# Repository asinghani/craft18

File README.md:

# Craft18

Bring Minecraft Redstone circuits to life using Craft18, our physical re-creation of the game’s “circuit” mechanics using only discrete analog components. Look ma, no microcontrollers! To build even more complex circuits, link the physical world to the virtual world using our custom game plugin and game-to-physical bridge!

Also see our [circuit diagrams PDF](doc/schem.pdf) to see how each circuit is implemented!

## Repo Structure

- [3D printable CAD models for each block](3d_cad/)
- [Texture images for each block](textures/)
- [Raw circuit schematic files](schematics/)
- [Spigot plugin for physical-to-virtual bridge](craft18_plugin/)
- [Software for physical-to-virtual bridge](craft18duino/)
- [Baseplate CAD files](2d_cad/)
- [Connector board layouts](boards/)

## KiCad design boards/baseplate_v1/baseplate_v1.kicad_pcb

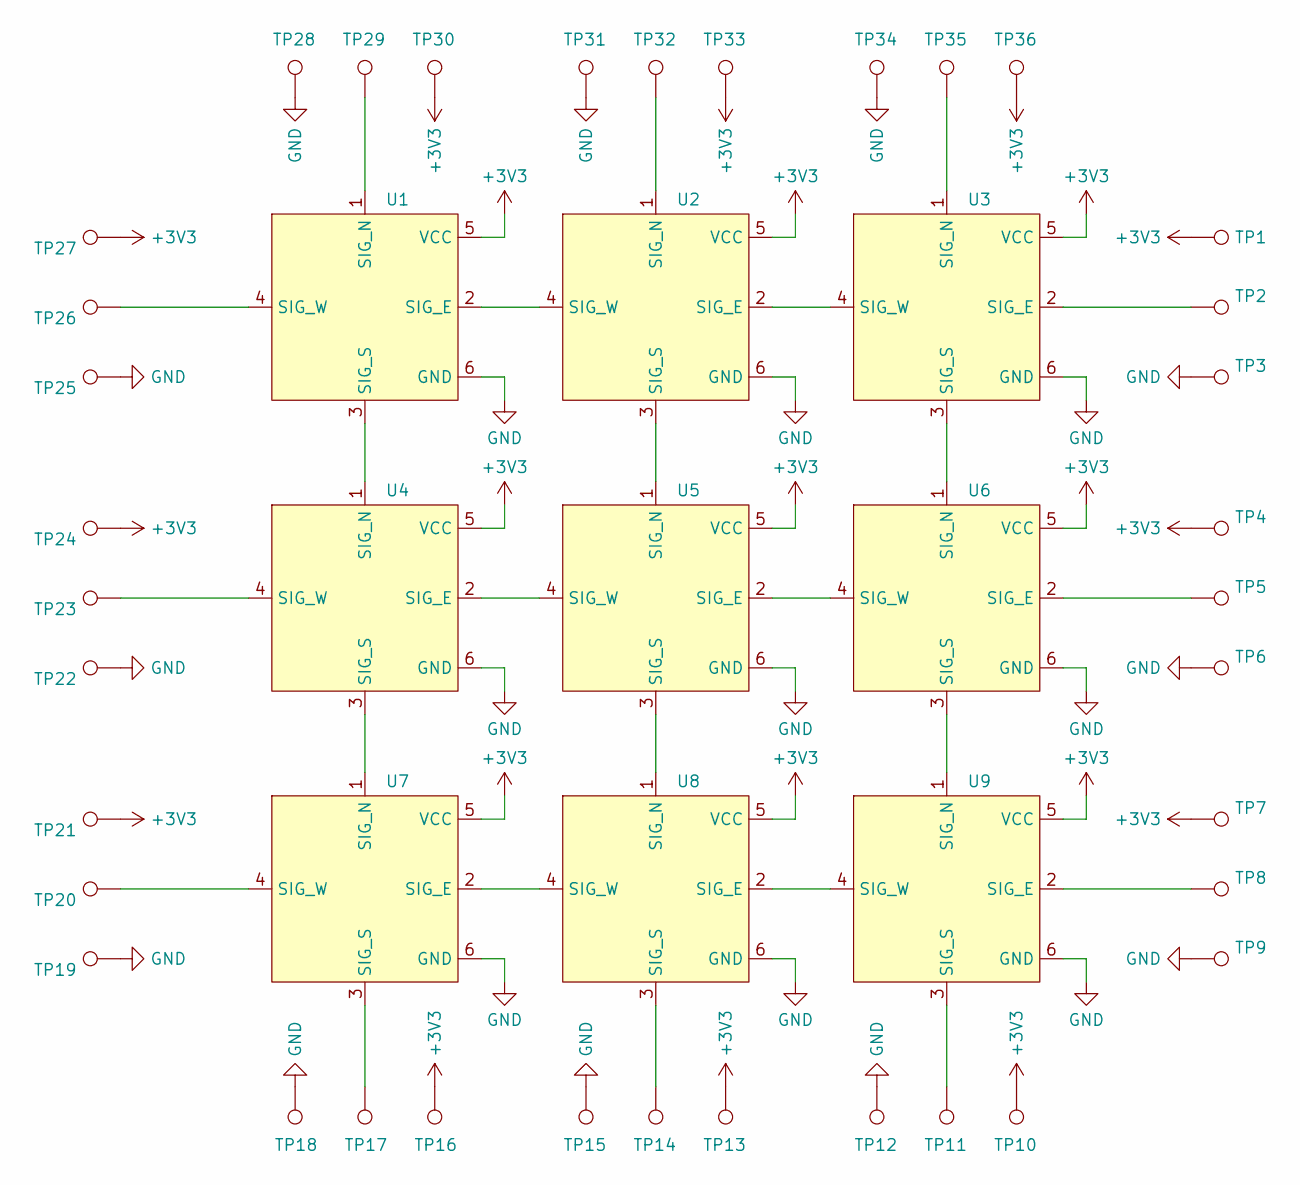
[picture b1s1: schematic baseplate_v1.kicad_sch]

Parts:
TP1, TP2, TP3, TP4, TP5, TP6, TP7, TP8, TP9, TP10, TP11, TP12, TP13, TP14, TP15, TP16, TP17, TP18, TP19, TP20, TP21, TP22, TP23, TP24, TP25, TP26, TP27, TP28, TP29, TP30, TP31, TP32, TP33, TP34, TP35, TP36: TestPoint; edge_pad
U1, U2, U3, U4, U5, U6, U7, U8, U9: 3x3conn

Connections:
+3V3: TP1.1, TP4.1, TP7.1, TP10.1, TP13.1, TP16.1, TP21.1, TP24.1, TP27.1, TP30.1, TP33.1, TP36.1, U1.5 (VCC), U2.5 (VCC), U3.5 (VCC), U4.5 (VCC), U5.5 (VCC), U6.5 (VCC), U7.5 (VCC), U8.5 (VCC), U9.5 (VCC)
GND: TP3.1, TP6.1, TP9.1, TP12.1, TP15.1, TP18.1, TP19.1, TP22.1, TP25.1, TP28.1, TP31.1, TP34.1, U1.6 (GND), U2.6 (GND), U3.6 (GND), U4.6 (GND), U5.6 (GND), U6.6 (GND), U7.6 (GND), U8.6 (GND), U9.6 (GND)
unnamed: U1.2 (SIG_E), U2.4 (SIG_W)
unnamed: TP29.1, U1.1 (SIG_N)
unnamed: U1.3 (SIG_S), U4.1 (SIG_N)
unnamed: TP26.1, U1.4 (SIG_W)
unnamed: U2.2 (SIG_E), U3.4 (SIG_W)
unnamed: TP32.1, U2.1 (SIG_N)
unnamed: U2.3 (SIG_S), U5.1 (SIG_N)
unnamed: TP2.1, U3.2 (SIG_E)
unnamed: TP35.1, U3.1 (SIG_N)
unnamed: U3.3 (SIG_S), U6.1 (SIG_N)
unnamed: U4.2 (SIG_E), U5.4 (SIG_W)
unnamed: U4.3 (SIG_S), U7.1 (SIG_N)
unnamed: TP23.1, U4.4 (SIG_W)
unnamed: U5.2 (SIG_E), U6.4 (SIG_W)
unnamed: U5.3 (SIG_S), U8.1 (SIG_N)
unnamed: TP5.1, U6.2 (SIG_E)
unnamed: U6.3 (SIG_S), U9.1 (SIG_N)
unnamed: U7.2 (SIG_E), U8.4 (SIG_W)
unnamed: TP17.1, U7.3 (SIG_S)
unnamed: TP20.1, U7.4 (SIG_W)
unnamed: U8.2 (SIG_E), U9.4 (SIG_W)
unnamed: TP14.1, U8.3 (SIG_S)
unnamed: TP8.1, U9.2 (SIG_E)
unnamed: TP11.1, U9.3 (SIG_S)

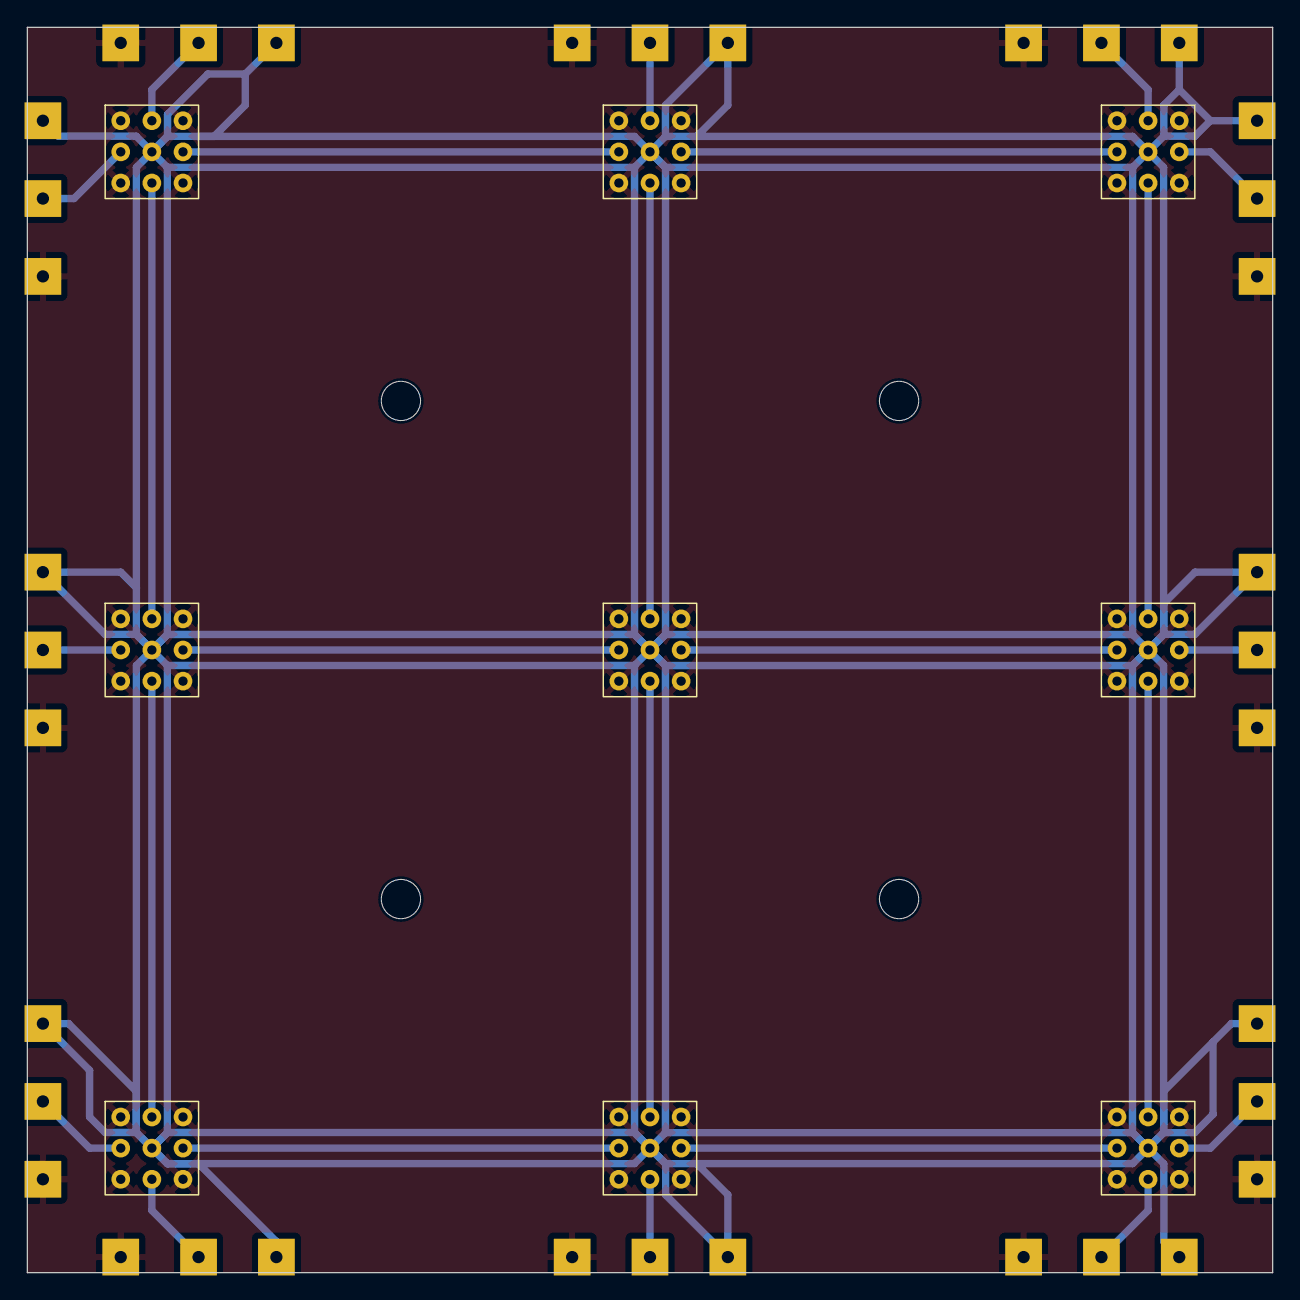
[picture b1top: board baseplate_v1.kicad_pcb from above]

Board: 2 copper layers, 101.6 x 101.6 mm, 45 parts (0 on the bottom side), 26 nets.

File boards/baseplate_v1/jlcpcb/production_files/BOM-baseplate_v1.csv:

Comment,Designator,Footprint,LCSC
TestPoint,TP9,edge_pad,
~,U9,3x3conn,
TestPoint,TP35,edge_pad,
TestPoint,TP11,edge_pad,
~,U5,3x3conn,
~,U1,3x3conn,
TestPoint,TP5,edge_pad,
TestPoint,TP25,edge_pad,
TestPoint,TP4,edge_pad,
~,U4,3x3conn,
TestPoint,TP20,edge_pad,
~,U8,3x3conn,
TestPoint,TP26,edge_pad,
TestPoint,TP31,edge_pad,
~,U3,3x3conn,
~,U2,3x3conn,
TestPoint,TP16,edge_pad,
TestPoint,TP27,edge_pad,
TestPoint,TP17,edge_pad,
TestPoint,TP8,edge_pad,
TestPoint,TP7,edge_pad,
TestPoint,TP19,edge_pad,
TestPoint,TP18,edge_pad,
TestPoint,TP34,edge_pad,
TestPoint,TP6,edge_pad,
TestPoint,TP12,edge_pad,
TestPoint,TP2,edge_pad,
TestPoint,TP15,edge_pad,
TestPoint,TP32,edge_pad,
TestPoint,TP30,edge_pad,
TestPoint,TP10,edge_pad,
~,U7,3x3conn,
TestPoint,TP29,edge_pad,
~,U6,3x3conn,
TestPoint,TP36,edge_pad,
TestPoint,TP28,edge_pad,
TestPoint,TP14,edge_pad,
TestPoint,TP1,edge_pad,
TestPoint,TP22,edge_pad,
TestPoint,TP33,edge_pad,
TestPoint,TP24,edge_pad,
TestPoint,TP13,edge_pad,
TestPoint,TP23,edge_pad,
TestPoint,TP21,edge_pad,
TestPoint,TP3,edge_pad,

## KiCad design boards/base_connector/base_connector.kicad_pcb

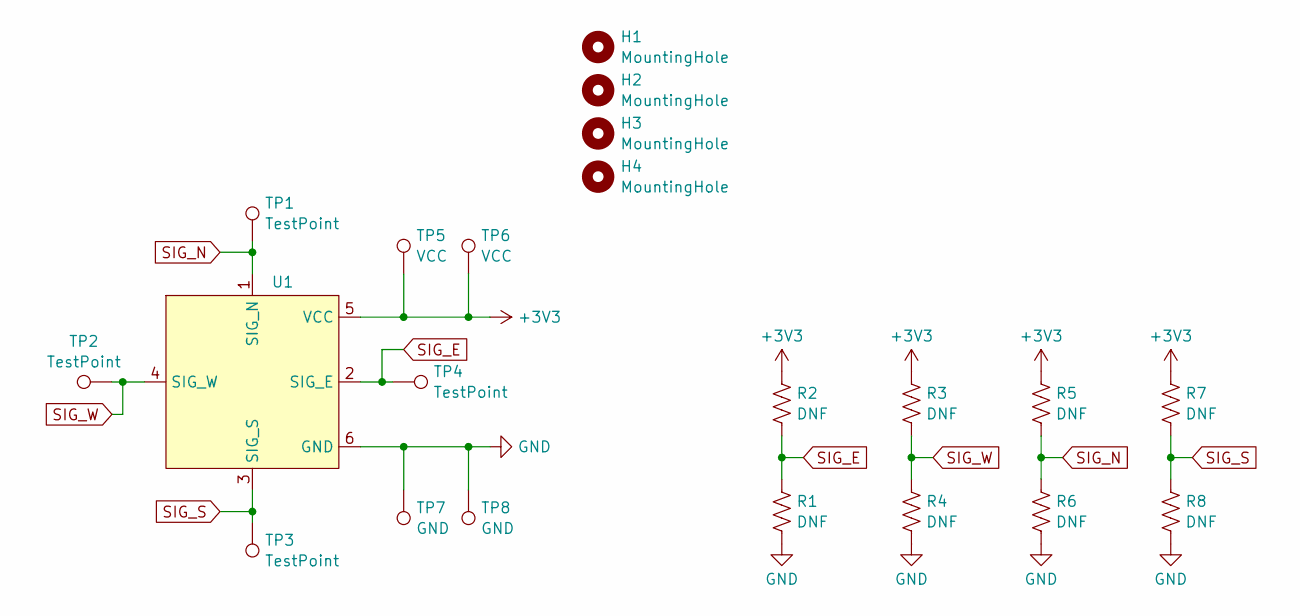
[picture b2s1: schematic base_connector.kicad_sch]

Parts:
H1, H2, H3, H4: MountingHole; MountingHole_3.2mm_M3
R1, R2, R3, R4, R5, R6, R7, R8: DNF; R_0805_2012Metric_Pad1.20x1.40mm_HandSolder
TP1, TP2, TP3, TP4: TestPoint; TestPoint_THTPad_2.5x2.5mm_Drill1.2mm
TP5, TP6: VCC; TestPoint_THTPad_2.5x2.5mm_Drill1.2mm
TP7, TP8: GND; TestPoint_THTPad_2.5x2.5mm_Drill1.2mm
U1: 3x3conn

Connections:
+3V3: R2.2, R3.2, R5.2, R7.2, TP5.1, TP6.1, U1.5 (VCC)
GND: R1.1, R4.1, R6.1, R8.1, TP7.1, TP8.1, U1.6 (GND)
SIG_E: R1.2, R2.1, TP4.1, U1.2 (SIG_E)
SIG_N: R5.1, R6.2, TP1.1, U1.1 (SIG_N)
SIG_S: R7.1, R8.2, TP3.1, U1.3 (SIG_S)
SIG_W: R3.1, R4.2, TP2.1, U1.4 (SIG_W)

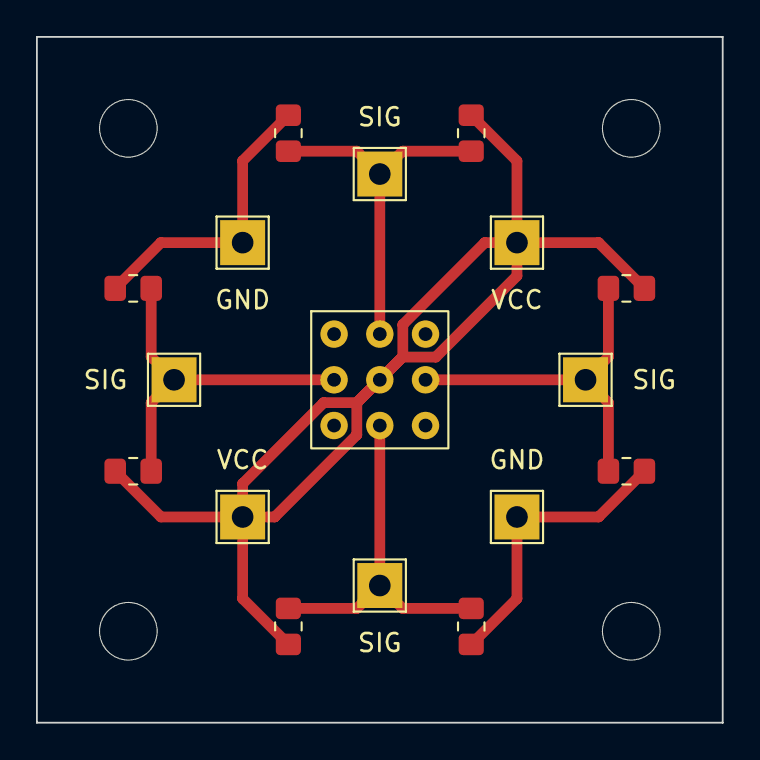
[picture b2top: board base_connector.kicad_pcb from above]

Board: 2 copper layers, 38.1 x 38.1 mm, 21 parts (0 on the bottom side), 6 nets.

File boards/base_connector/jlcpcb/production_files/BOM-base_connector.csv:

Comment,Designator,Footprint,LCSC
MountingHole,H2,MountingHole_3.2mm_M3,
DNF,R8,R_0805_2012Metric_Pad1.20x1.40mm_HandSolder,
VCC,TP5,TestPoint_THTPad_2.5x2.5mm_Drill1.2mm,
TestPoint,TP1,TestPoint_THTPad_2.5x2.5mm_Drill1.2mm,
GND,TP7,TestPoint_THTPad_2.5x2.5mm_Drill1.2mm,
MountingHole,H1,MountingHole_3.2mm_M3,
DNF,R7,R_0805_2012Metric_Pad1.20x1.40mm_HandSolder,
MountingHole,H4,MountingHole_3.2mm_M3,
DNF,R2,R_0805_2012Metric_Pad1.20x1.40mm_HandSolder,
~,U1,3x3conn,
DNF,R5,R_0805_2012Metric_Pad1.20x1.40mm_HandSolder,
TestPoint,TP4,TestPoint_THTPad_2.5x2.5mm_Drill1.2mm,
VCC,TP6,TestPoint_THTPad_2.5x2.5mm_Drill1.2mm,
TestPoint,TP3,TestPoint_THTPad_2.5x2.5mm_Drill1.2mm,
DNF,R4,R_0805_2012Metric_Pad1.20x1.40mm_HandSolder,
GND,TP8,TestPoint_THTPad_2.5x2.5mm_Drill1.2mm,
DNF,R1,R_0805_2012Metric_Pad1.20x1.40mm_HandSolder,
MountingHole,H3,MountingHole_3.2mm_M3,
TestPoint,TP2,TestPoint_THTPad_2.5x2.5mm_Drill1.2mm,
DNF,R3,R_0805_2012Metric_Pad1.20x1.40mm_HandSolder,
DNF,R6,R_0805_2012Metric_Pad1.20x1.40mm_HandSolder,

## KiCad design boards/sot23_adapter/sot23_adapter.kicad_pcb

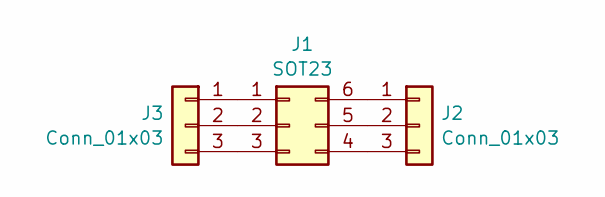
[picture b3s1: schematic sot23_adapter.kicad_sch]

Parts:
J1: SOT23; TSOT-23-6_HandSoldering
J2, J3: Conn_01x03; PinHeader_1x03_P2.54mm_Vertical

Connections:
unnamed: J1.1, J3.1
unnamed: J1.2, J3.2
unnamed: J1.3, J3.3
unnamed: J1.4, J2.3
unnamed: J1.5, J2.2
unnamed: J1.6, J2.1

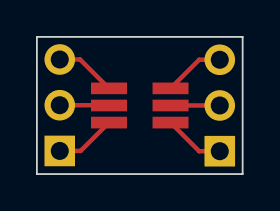
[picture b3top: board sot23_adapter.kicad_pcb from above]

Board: 2 copper layers, 11.4 x 7.6 mm, 3 parts (0 on the bottom side), 6 nets.

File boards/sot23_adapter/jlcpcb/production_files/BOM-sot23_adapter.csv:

Comment,Designator,Footprint,LCSC
Conn_01x03,J3,PinHeader_1x03_P2.54mm_Vertical,
Conn_01x03,J2,PinHeader_1x03_P2.54mm_Vertical,
SOT23,J1,TSOT-23-6_HandSoldering,

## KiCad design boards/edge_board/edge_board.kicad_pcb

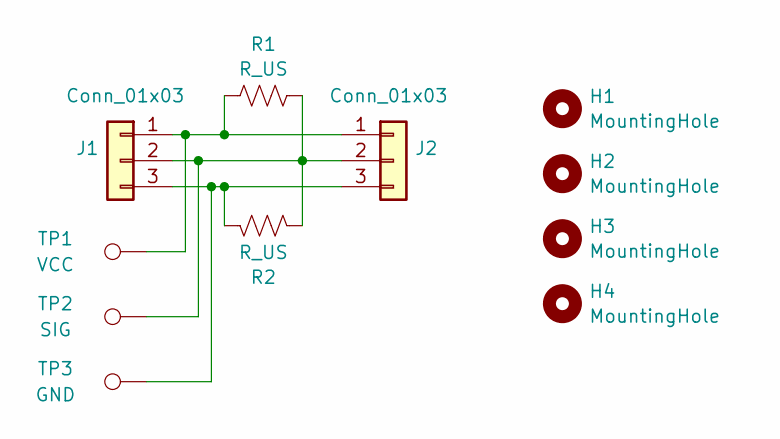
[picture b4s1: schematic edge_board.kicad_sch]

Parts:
H1, H2, H3, H4: MountingHole; MountingHole_2.2mm_M2
J1: Conn_01x03; connmale
J2: Conn_01x03; connfemale
R1, R2: R_US; R_0805_2012Metric_Pad1.20x1.40mm_HandSolder
TP1: VCC; TestPoint_THTPad_3.0x3.0mm_Drill1.5mm
TP2: SIG; TestPoint_THTPad_3.0x3.0mm_Drill1.5mm
TP3: GND; TestPoint_THTPad_3.0x3.0mm_Drill1.5mm

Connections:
unnamed: J1.1, J2.1, R1.1, TP1.1
unnamed: J1.2, J2.2, R1.2, R2.1, TP2.1
unnamed: J1.3, J2.3, R2.2, TP3.1

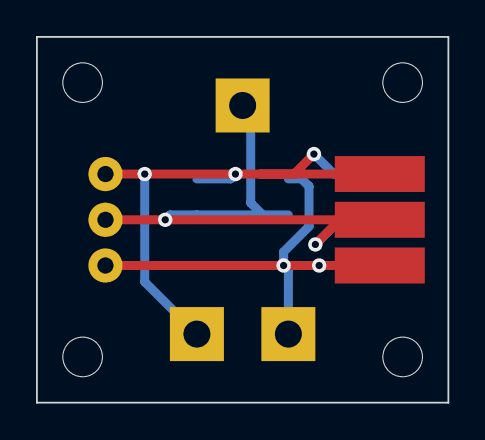
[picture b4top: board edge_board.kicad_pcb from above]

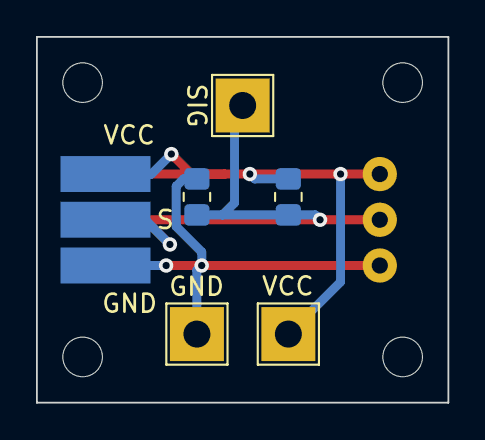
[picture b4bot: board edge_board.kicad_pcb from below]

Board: 2 copper layers, 22.9 x 20.3 mm, 11 parts (5 on the bottom side), 3 nets.

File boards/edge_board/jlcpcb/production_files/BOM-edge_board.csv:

Comment,Designator,Footprint,LCSC
MountingHole,H2,MountingHole_2.2mm_M2,
MountingHole,H4,MountingHole_2.2mm_M2,
Conn_01x03,J2,connfemale,
MountingHole,H3,MountingHole_2.2mm_M2,
MountingHole,H1,MountingHole_2.2mm_M2,
Conn_01x03,J1,connmale,
SIG,TP2,TestPoint_THTPad_3.0x3.0mm_Drill1.5mm,
R_US,R1,R_0805_2012Metric_Pad1.20x1.40mm_HandSolder,
VCC,TP1,TestPoint_THTPad_3.0x3.0mm_Drill1.5mm,
GND,TP3,TestPoint_THTPad_3.0x3.0mm_Drill1.5mm,
R_US,R2,R_0805_2012Metric_Pad1.20x1.40mm_HandSolder,

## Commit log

2024-01-15 start
2024-01-16 add plugin and arduino code
2024-01-16 add simple textures
2024-01-16 added redstone and grass textures
2024-01-16 add buttons
2024-01-16 add comparator/repeater/oak planks/smooth stone
2024-01-19 add planks
2024-01-20 add the rest of the pins for arduino
2024-01-21 add CAD files
2024-01-21 add additional CAD files
2024-01-21 notes
2024-01-21 docs
2024-01-21 Add electronic schematics
2024-01-21 Add docs and make public
2024-01-21 Fix link
2024-01-21 Public release
2024-01-21 Final code used for demo
